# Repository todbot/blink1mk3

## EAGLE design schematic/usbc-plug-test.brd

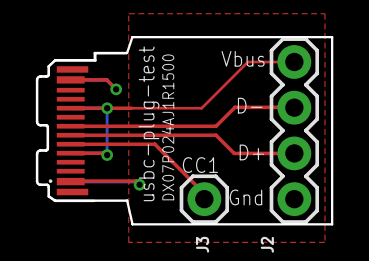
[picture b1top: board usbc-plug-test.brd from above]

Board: 2 copper layers, 16.4 x 10.4 mm, 3 parts (0 on the bottom side), 5 nets.

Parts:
J1: DX07P024AJ1R1500; JAE_DX07P024AJ1R1500
J2: 1X04
J3: 1X01

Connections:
+5V: J1.A4, J1.A9, J1.B4, J1.B9, J2.4
CC: J1.A5, J3.1
GND: J1.A1, J1.A12, J1.B1, J1.B12, J2.1
USB_D+: J1.A6, J2.2
USB_D-: J1.A7, J2.3

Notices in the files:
parts and their libraries:
SparkFun-Connectors: Licensing: Creative Commons ShareAlike 4.0 International - https://creativecommons.org/licenses/by-sa/4.0
